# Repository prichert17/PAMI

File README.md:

# Projet PAMI (2025-2026) - Eurobot

Ce dépôt documente le projet PAMI (Petit Actionneur Motorisé Indépendant) sur lequel j'ai travaillé pendant un an, dans le cadre de la coupe Eurobot 2026. Il centralise l'ensemble de la conception matérielle (deux PCB, structure mécanique) et logicielle du robot. 

<p align="center">
  
  <br>
  <em>Légende : Photo du robot PAMI assemblé</em>
</p>

<p align="center">
  
  <br>
  <em>Légende : Rendu 3D du robot (Fusion 360)</em>
</p>

## Codes principaux

Pour mieux comprendre l'architecture du système, voici les trois éléments importants du dépôt :

*   **[`PAMI_2026/`](./Projects/PAMI_2026)** : Contient le code haut niveau qui est exécuté sur le microcontrôleur **ESP32**.
*   **[`Projects/Asservissement_G4/`](./Projects/Asservissement_G4)** : Contient tout le code de l'asservissement, de l'odométrie et le contrôle des moteurs. Ce code tourne sur la carte **NUCLEO-G431KB** (STM32).
*   **[`Projects/IHM_PAMI_2026.py`](./Projects/IHM_PAMI_2026.py)** : Une interface homme-machine (IHM) développée en Python qui permet de lire et visualiser en temps réel les coordonnées et l'état du PAMI lors des phases de tests.

---

## Architecture Bas Niveau : PCB Principal (Contrôle Moteurs & Alimentation)

Le robot dispose de deux cartes électroniques (PCB). La partie bas niveau, gérée par le PCB principal s'occupe de l'alimentation générale et de la motricité du robot. Le PAMI est assez compact : ses dimensions finales sont de 10.5cm par 19cm avec ses bras repliés (et 24cm bras dépliés), ce qui a imposé des contraintes sur le routage du circuit et le choix des composants.

### 1. Gestion de la Batterie et Alimentation
Le robot est alimenté par une unique cellule de batterie LiFePO4 au format 26650. Le circuit d'alimentation a subi plusieurs modifications suite à des problèmes rencontrés lors du développement :

*   **Le choix du LiFePO4 :** Bien que l'intégration de cette chimie ait rendu la conception du circuit d'alimentation plus complexe (notamment pour la régulation de tension, le prix plus élevé), c'est un choix qui reste très avantageux. Le LiFePO4 est extrêmement sécurisé (aucun risque d'incendie, pas besoin de sac ignifugé contrairement aux batteries LiPo), il offre un excellent courant de décharge (15A) pour les moteurs, et l'utilisation d'une seule et unique cellule simplifie grandement le processus de charge (pas d'équilibrage entre deux cellules nécessaire).
*   **Port USB C intégré :** Pour une simplicité d'usage maximale, un port USB C standard a été intégré au design, permettant de recharger facilement la batterie avec n'importe quel chargeur ou batterie externe.
*   **Circuit de Charge :** La charge est gérée directement sur le PCB par un composant dédié à ce type de batterie, le **CN3058E**, avec des LEDs indicatrices (Charge en cours / Charge terminée).
*   **Sécurité Batterie :** La batterie est surveillée par un IC de protection **HY2112**, associé à un double MOSFET N-Channel (FS8205A) pour couper le circuit en cas de problème.
*   **Régulation de tension :** La tension de la cellule LiFePO4 pouvant monter à 3.6V (ce qui est trop élevé pour l'ESP32 et certains capteurs), j'ai opté pour un convertisseur **Buck-Boost (TPS63000)** au lieu d'un simple circuit Boost. Il assure un 3.3V parfaitement stable en abaissant ou élevant la tension de la batterie selon les besoins, pour un courant jusqu'à 1A.
*   **Le problème des appels de courant :** Un problème est survenu avec l'alimentation des servomoteurs. Leurs appels de courant créaient d'énormes chutes de tension (la tension de la batterie chutait jusqu'à 2.4V pendant un court instant). Le robot ne parvenait pas à se lever de manière autonome, la tension de la batterie passait en dessous du seuil limite du circuit boost 6V. La cause : la résistance interne du boitier de la batterie 26650 et des pistes de cuivre trop fines (1.5mm) qui ne supportaient pas les pics d'intensité très élevés (pouvant monter jusqu'à 3A sur le rail 6V, soit quasiment 6A en sortie de la batterie). Le problème a été résolu en soudant un condensateur de 2200µF (10V) directement à l'entrée du boost 6V pour agir comme une réserve d'énergie, ce qui diminuait fortement la chute de tension.

### 2. Odométrie et Asservissement (NUCLEO-G431KB)
La carte intègre un microcontrôleur STM32 (NUCLEO-G431KB) programmé en C++ pour gérer la dynamique temps-réel du robot. Un travail conséquent a été réalisé sur la fiabilité des déplacements et la prévention du patinage.

*   **Odométrie Haute Fréquence (500Hz) :** La position exacte du robot (X, Y, Angle) est calculée 500 fois par seconde. Les encodeurs incrémentiels des roues renvoient des signaux en quadrature décodés de manière purement matérielle par les Timers du STM32. Le code gère les débordements de compteurs (overflow des timers 16 bits) pour assurer un suivi sans erreur.
*   **Asservissement PID en 2 Phases (100Hz) :** Le contrôle de la trajectoire s'effectue via une boucle PID (Proportionnel, Intégral, Dérivé) actualisée à 100Hz. Pour rejoindre une cible, l'algorithme utilise une logique en deux temps :
    1. **Rotation pure :** Le robot pivote sur lui-même pour s'aligner parfaitement vers sa cible.
    2. **Avance avec correction :** Une fois aligné, il avance en ligne droite tout en maintenant son angle de manière active. Si le robot doit dévier fortement, la commande linéaire est automatiquement réduite pour privilégier la rotation et garder un mouvement fluide.
*   **Traction Control & Anti-Patinage :** Les robots de la coupe Eurobot sont sujets au patinage (poussière, accélération forte), ce qui fausse instantanément l'odométrie. J'ai donc un algorithme de détection de glissement : si la différence de vitesse mesurée entre la roue gauche et droite devient anormalement élevée, le STM32 détecte la perte d'adhérence et réduit la commande PWM envoyée aux moteurs.
*   **Performances :** À pleine vitesse, les moteurs tournent à environ 5 tours/seconde, propulsant le PAMI à 68 cm/s (2.4 km/h). La dérive odométrique pure a été mesurée à environ 2cm d'erreur pour 1 mètre parcouru en ligne droite.
*   **Communication Inter-Cartes :** Le STM32 transmet continuellement ses données d'odométrie et son état au cerveau central (l'ESP32) via une liaison série (UART), dont le protocole est détaillé dans `pami_com.h`.

<p align="center">
  
  <br>
  <em>Légende : Schéma de l'architecture d'asservissement du STM32.</em>
</p>

### Schématique du PCB Principal

Voici la schématique électrique du PCB principal (Moteurs & Alimentation) montrant l'interconnexion entre la NUCLEO, les drivers moteurs, le circuit de charge de la batterie et le régulateur Buck-Boost :

<p align="center">
  
  <br>
  <em>Légende : Schématique détaillée du PCB d'alimentation</em>
</p>

<p align="center">
  
  <br>
  <em>Légende : Routage du PCB d'alimentation</em>
</p>

## Architecture Haut Niveau : Capteurs et Stratégie (ESP32)

La seconde carte du robot embarque un **ESP32**. Ce microcontrôleur fait office de cerveau principal : il ne gère pas les moteurs principaux directement, mais s'occupe de la prise de décision, de la vision spatiale (capteurs ToF matriciels), de la gestion du temps de match et de l'interface utilisateur.

### 1. Multitâche avec FreeRTOS
Pour garantir une réactivité maximale sans bloquer le système lors de la lecture des capteurs I2C (qui peut être lente), le code de l'ESP32 est architecturé autour du système d'exploitation temps réel **FreeRTOS**. Les tâches sont réparties sur les deux cœurs (Cores) physiques du processeur :

*   **Core 1 (Haute Priorité) :** 
    *   `Task_Comms` : Écoute en continu le port série UART pour ne rater aucune mise à jour de position venant du STM32. Permet aussi le debug lorsque branché à un PC.
    *   `Task_Strategy` : La machine à états principale du robot. Elle dicte les déplacements et gère le chronomètre du match.
*   **Core 0 (Basse Priorité) :**
    *   `Task_Tofs` : Gère le multiplexage et l'acquisition des données des 3 capteurs de distance matriciels sur le bus I2C.
    *   `Task_IHM` : Contrôle les animations de la LED d'état WS2812B et pilote les servomoteurs d'actionnement de fin de match.

### 2. Vision Spatiale : Capteurs ToF (VL53L5CX) et Anti-Collision
Le robot est équipé de 3 capteurs Time-of-Flight matriciels **VL53L5CX** (Centre, Gauche, Droite) configurés en résolution 8x8 zones à 15 Hz.

*  L'ESP32 configure dynamiquement les adresses I2C des 3 capteurs au démarrage (vers `0x30`, `0x31`, `0x32`) en utilisant les broches `XSHUT` (LPN), ce qui permet de tous les utiliser sur le même bus I2C à 400kHz.
*   **Calcul de repère absolu :** Lorsqu'un capteur détecte un obstacle, la tâche ne se contente pas de renvoyer une distance. Elle utilise la position instantanée du robot (X, Y, θ) et la géométrie des capteurs (FOV de 45°/60°, offset physique en X/Y) pour projeter l'obstacle sur le système de coordonnées du terrain. Le robot sait exactement où se trouve l'obstacle sur la table.
*   **Évitement d'urgence :** Si un objet est détecté à moins de 10 cm dans les zones critiques, le STM32 reçoit instantanément un ordre d'arrêt (`stopMotors()`) via l'UART. Le robot se met en pause et reprend sa route de lui-même dès que l'obstacle disparaît.

### 3. Stratégie et Machine à États
La logique de match est dictée par une machine à états :

1.  **`STATE_WAIT` (Attente) :** L'ESP32 lit la couleur de l'équipe via un switch (`PIN_SW_COLOR`). L'ensemble du système de coordonnées (points de départ, waypoints, cibles) est automatiquement symétrisée (inversion de l'axe X) si le robot est dans l'équipe bleue. Le robot attend le retrait de la tirette, en affichant la couleur du terrain sur la led d'IHM.
2.  **`STATE_DELAY` (Attente 85s) :** Selon les règles, les PAMI ne peuvent entrer en action qu'à la fin du match principal. Au retrait de la tirette, le robot reset son odométrie (`resetSTM32`) puis attend pendant 85 secondes.
3.  **`STATE_GAME` (Match) :** L'ESP32 commence à lire sa route de Waypoints et envoie les coordonnées cibles au STM32. Si un obstacle fixe est détecté lors du premier déplacement, un waypoint bonus est généré dynamiquement pour modifier la stratégie en cours de match.
4.  **`STATE_END` (Fin de match) :** À T+99s, le robot stoppe ses moteurs et déploie ses bras à l'aide de ses servomoteurs.

### 4. Communication Inter-Cartes et IHM
*   **Protocole UART :** L'ESP32 et le STM32 communiquent à 115200 bauds. Le STM32 "stream" en continu ses coordonnées au format `X:123,Y:456,Z:1.57`, que l'ESP32 parse via la fonction `parseSTM32Data`. En retour, l'ESP32 envoie des commandes simples au STM32 (`mode auto`, `stop`, `X:1000`, `reset:x:y:z`).
*   **Feedback Visuel (LED WS2812B) :** Sans écran, le debug visuel repose principalement sur la LED RGB adressable intelligente. Sa couleur et son rythme de clignotement indiquent instantanément l'état du système : 
    *   *Rouge fixe* : Batterie LiFePO4 faible.
    *   *Orange clignotant* : Obstacle détecté par ToF.
    *   *Vert clignotant* : Tirette retirée, en cours d'attente (85s).
    *   *Vert fixe* : Match en cours.
    *   *Jaune/Bleu* : Robot en attente de la tirette, affiche la couleur de l'équipe sélectionnée.

### 5. Conception de la Carte ESP32 (PCB Haut Niveau)
Pour centraliser toutes ces fonctionnalités, un second PCB a été conçu spécifiquement pour accueillir l'ESP32. Cette carte vient se superposer à la carte d'alimentation principale et gère toute la logique périphérique :

*   **L'Interface Utilisateur (Switchs et LED) :** La carte intègre directement 3 interrupteurs (`DEBUG` pour l'affichage des logs, `TERRAIN` pour le choix de la couleur, et `MODE` pour basculer entre le mode automatique et le contrôle manuel via manette bluetooth), le connecteur pour la `Tirette` de démarrage, ainsi que la LED d'état WS2812B.
*   **Les Capteurs ToF :** Le routage contient aussi les 3 capteurs VL53L5CX (avec les angles adéquats pour couvrir l'avant du robot). On y retrouve le bus I2C commun (SDA/SCL) ainsi que les broches dédiées `LPN1`, `LPN2`, et `LPN3` permettant d'allumer les capteurs séquentiellement pour modifier leur adresse I2C au boot.
*   **Les Actionneurs (Servomoteurs) :** 3 connecteurs pour servomoteurs (`SERVO m1`, `SERVO m2`, `SERVO m3`) sont présents. Ils sont alimentés directement par le rail **6V** provenant de la carte principale, et commandés par des broches PWM de l'ESP32. Des condensateurs de 100µF sont placés au plus près des connecteurs pour lisser les appels de courant.
*   **Interconnexion :** Le connecteur `COMM_inter_mcu` assure la liaison avec la carte STM32 pour l'UART (TX/RX), les alimentations (3.3V et 6V), et les deux moteurs auxiliaires posés sur l'actionneur du robot qui lui permette de gravire des obstacles.

Voici la schématique et le routage de cette seconde carte :

<p align="center">
  
  <br>
  <em>Légende : Schématique détaillée du PCB ESP32 (Capteurs, IHM, Servos)</em>
</p>

<p align="center">
  
  <br>
  <em>Légende : Routage du PCB ESP32</em>
</p>

---

## Conclusion et Démonstration en Match

Après de nombreuses itérations matérielles (sur les deux itérations de PCB et la mécanique) ainsi qu'un gros travail d'optimisation logicielle, le PAMI a su remplir son rôle de manière fiable et concluante.

Voici une courte vidéo démontrant son fonctionnement lors d'un match (cas le plus simple, sans obstacles) :

https://github.com/user-attachments/assets/42d38b15-34ad-48e5-a77b-8a1eeed6a4e9

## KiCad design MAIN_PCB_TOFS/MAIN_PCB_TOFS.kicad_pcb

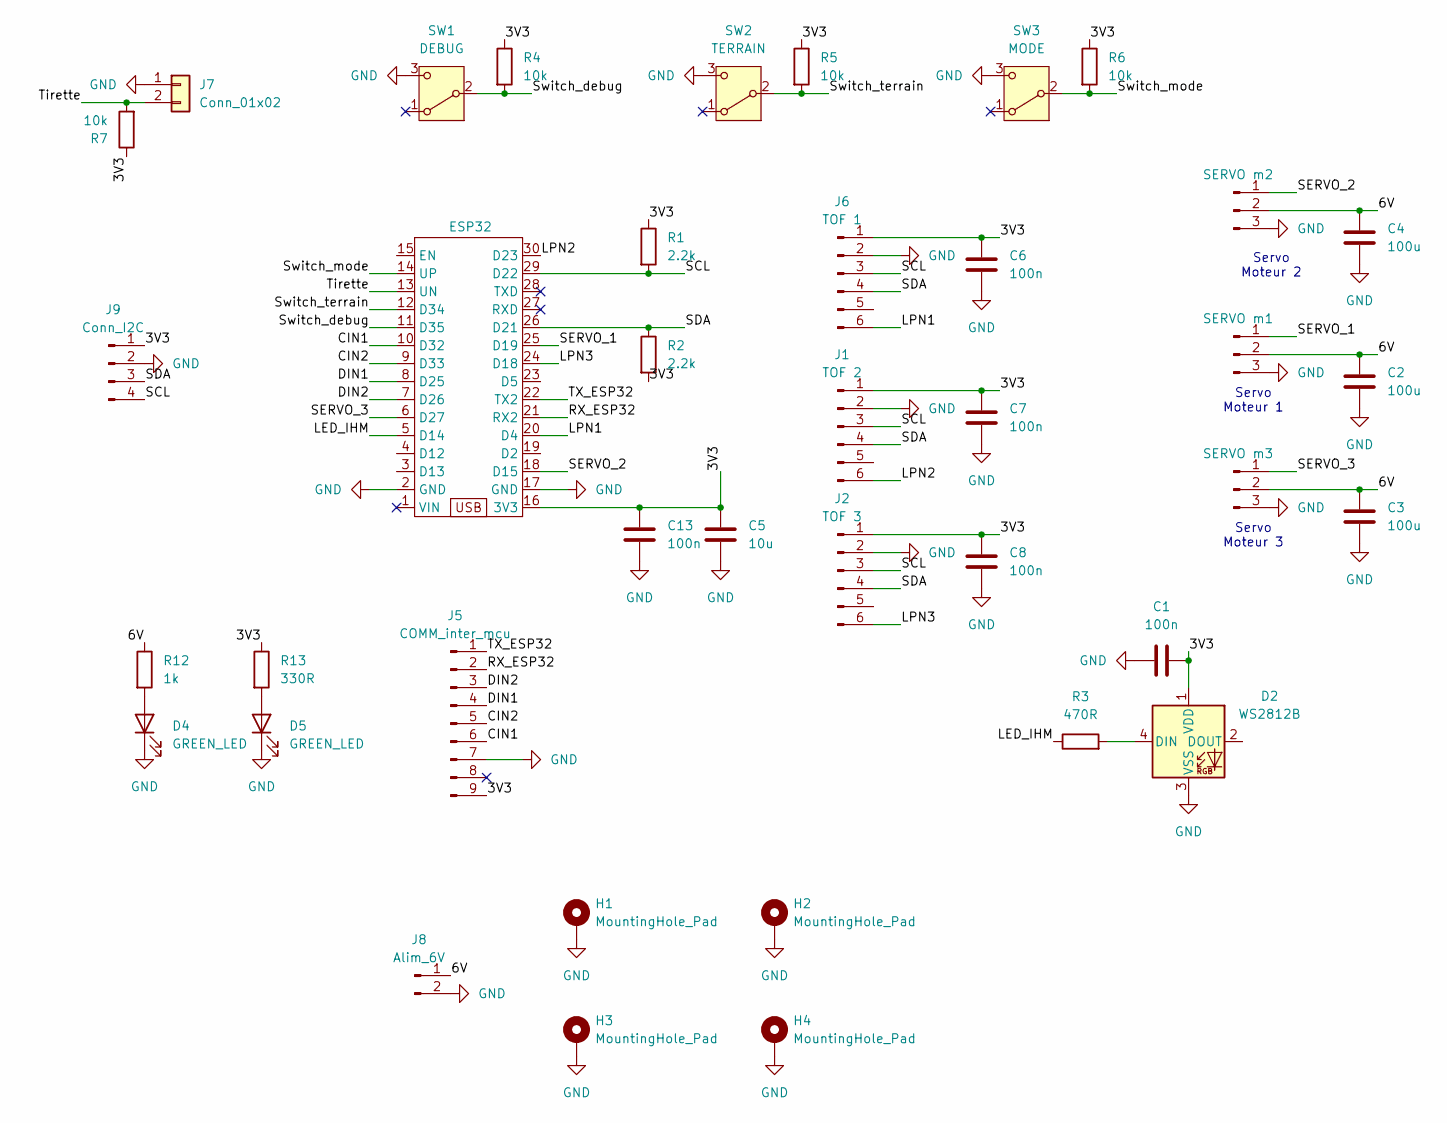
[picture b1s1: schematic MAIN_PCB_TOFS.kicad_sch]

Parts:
C1, C6, C7, C8, C13: 100n; C_0603_1608Metric
C2, C3, C4: 100u; CP_Elec_6.3x5.8
C5: 10u; C_0603_1608Metric
D2: WS2812B; LED_WS2812B_PLCC4_5.0x5.0mm_P3.2mm
D4, D5: GREEN_LED; LED_0603_1608Metric
H1, H2, H3, H4: MountingHole_Pad; MountingHole_3.2mm_M3_Pad_Via
J1: TOF 2; PinHeader_1x06_P2.54mm_Vertical
J2: TOF 3; PinHeader_1x06_P2.54mm_Vertical
J3: SERVO m2; PinHeader_1x03_P2.54mm_Vertical
J4: SERVO m1; PinHeader_1x03_P2.54mm_Vertical
J5: COMM_inter_mcu; PinSocket_1x09_P2.54mm_Vertical
J6: TOF 1; PinHeader_1x06_P2.54mm_Vertical
J7: Conn_01x02; PinHeader_1x02_P2.54mm_Vertical
J8: Alim_6V; JST_VH_B2P-VH_1x02_P3.96mm_Vertical
J9: Conn_I2C; PinHeader_1x04_P2.54mm_Vertical
J12: SERVO m3; PinHeader_1x03_P2.54mm_Vertical
R1, R2: 2.2k; R_0603_1608Metric
R3: 470R; R_0603_1608Metric
R4, R5, R6, R7: 10k; R_0603_1608Metric
R12: 1k; R_0603_1608Metric
R13: 330R; R_0603_1608Metric
SW1: DEBUG; SW_SPDT_PCM12
SW2: TERRAIN; SW_SPDT_PCM12
SW3: MODE; SW_SPDT_PCM12
U1: ESP32; DIP-30_W25.4mm_LongPads_esp32

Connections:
/3V3: C1.2, C5.1, C6.1, C7.1, C8.1, C13.1, D2.1 (VDD), J1.1, J2.1, J5.9, J6.1, J9.1, R1.1, R2.2, R4.1, R5.1, R6.1, R7.1, R13.1, U1.16 (3V3)
/6V: C2.1, C3.1, C4.1, J3.2, J4.2, J8.1, J12.2, R12.1
/CIN1: J5.6, U1.10 (D32)
/CIN2: J5.5, U1.9 (D33)
/DIN1: J5.4, U1.8 (D25)
/DIN2: J5.3, U1.7 (D26)
/LED_IHM: R3.1, U1.5 (D14)
/LPN1: J6.6, U1.20 (D4)
/LPN2: J1.6, U1.30 (D23)
/LPN3: J2.6, U1.24 (D18)
/RX_ESP32: J5.2, U1.21 (RX2)
/SCL: J1.3, J2.3, J6.3, J9.4, R1.2, U1.29 (D22)
/SDA: J1.4, J2.4, J6.4, J9.3, R2.1, U1.26 (D21)
/SERVO_1: J4.1, U1.25 (D19)
/SERVO_2: J3.1, U1.18 (D15)
/SERVO_3: J12.1, U1.6 (D27)
/Switch_debug: R4.2, SW1.2 (B), U1.11 (D35)
/Switch_mode: R6.2, SW3.2 (B), U1.14 (UP)
/Switch_terrain: R5.2, SW2.2 (B), U1.12 (D34)
/TX_ESP32: J5.1, U1.22 (TX2)
/Tirette: J7.2, R7.2, U1.13 (UN)
GND: C1.1, C2.2, C3.2, C4.2, C5.2, C6.2, C7.2, C8.2, C13.2, D2.3 (VSS), D4.1 (K), D5.1 (K), H1.1, H2.1, H3.1, H4.1, J1.2, J2.2, J3.3, J4.3, J5.7, J6.2, J7.1, J8.2, J9.2, J12.3, SW1.3 (C), SW2.3 (C), SW3.3 (C), U1.2 (GND), U1.17 (GND)
unnamed: D2.4 (DIN), R3.2
unnamed: D4.2 (A), R12.2
unnamed: D5.2 (A), R13.2

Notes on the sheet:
Servo Moteur 2
Servo Moteur 1
Servo Moteur 3

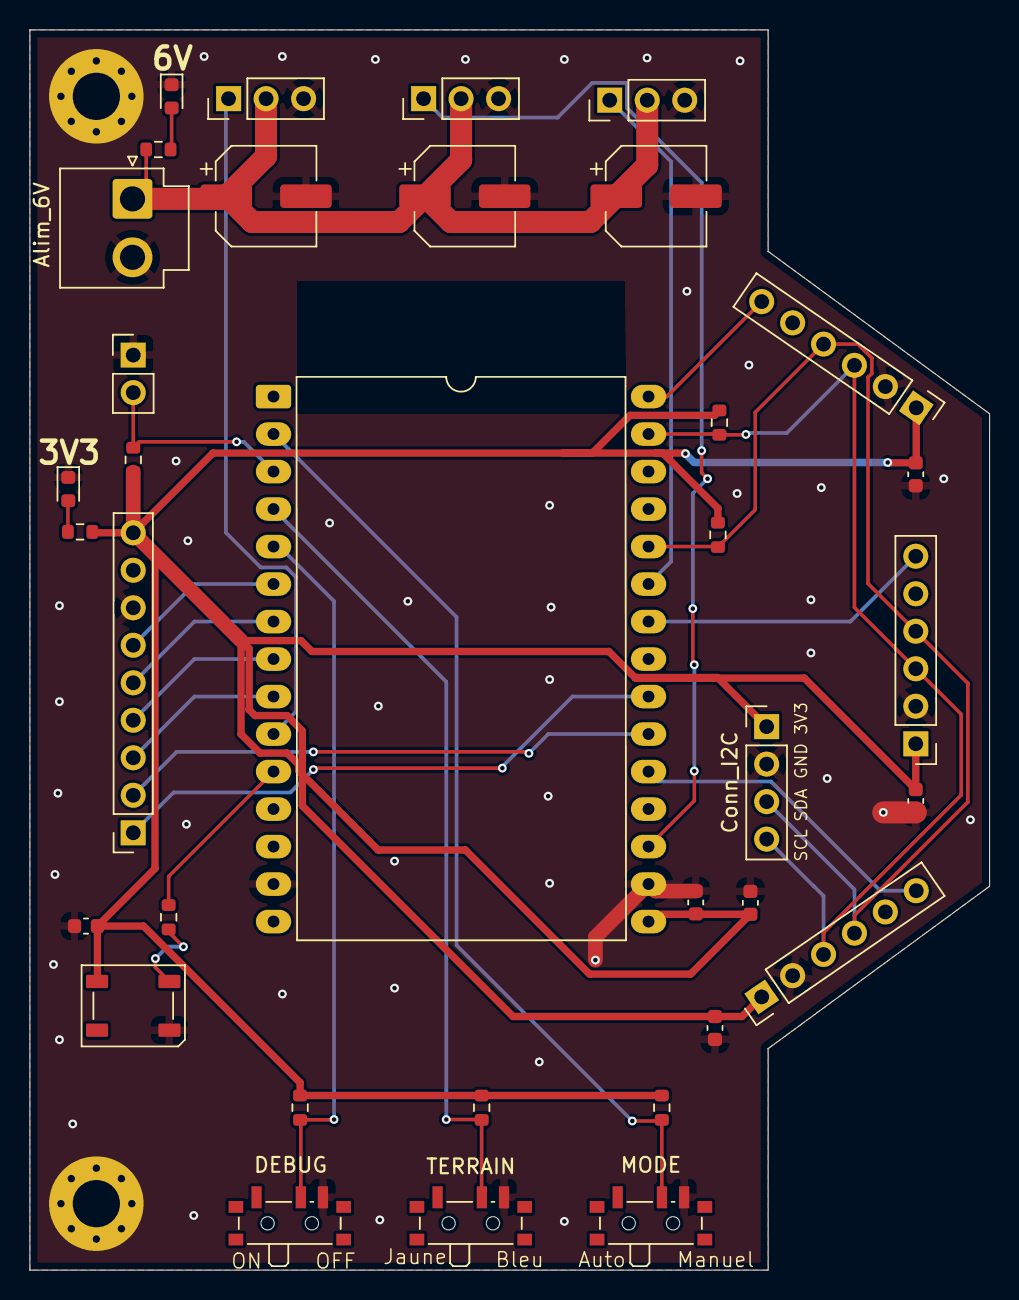
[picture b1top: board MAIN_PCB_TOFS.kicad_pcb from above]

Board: 2 copper layers, 65.0 x 84.0 mm, 37 parts (0 on the bottom side), 25 nets.

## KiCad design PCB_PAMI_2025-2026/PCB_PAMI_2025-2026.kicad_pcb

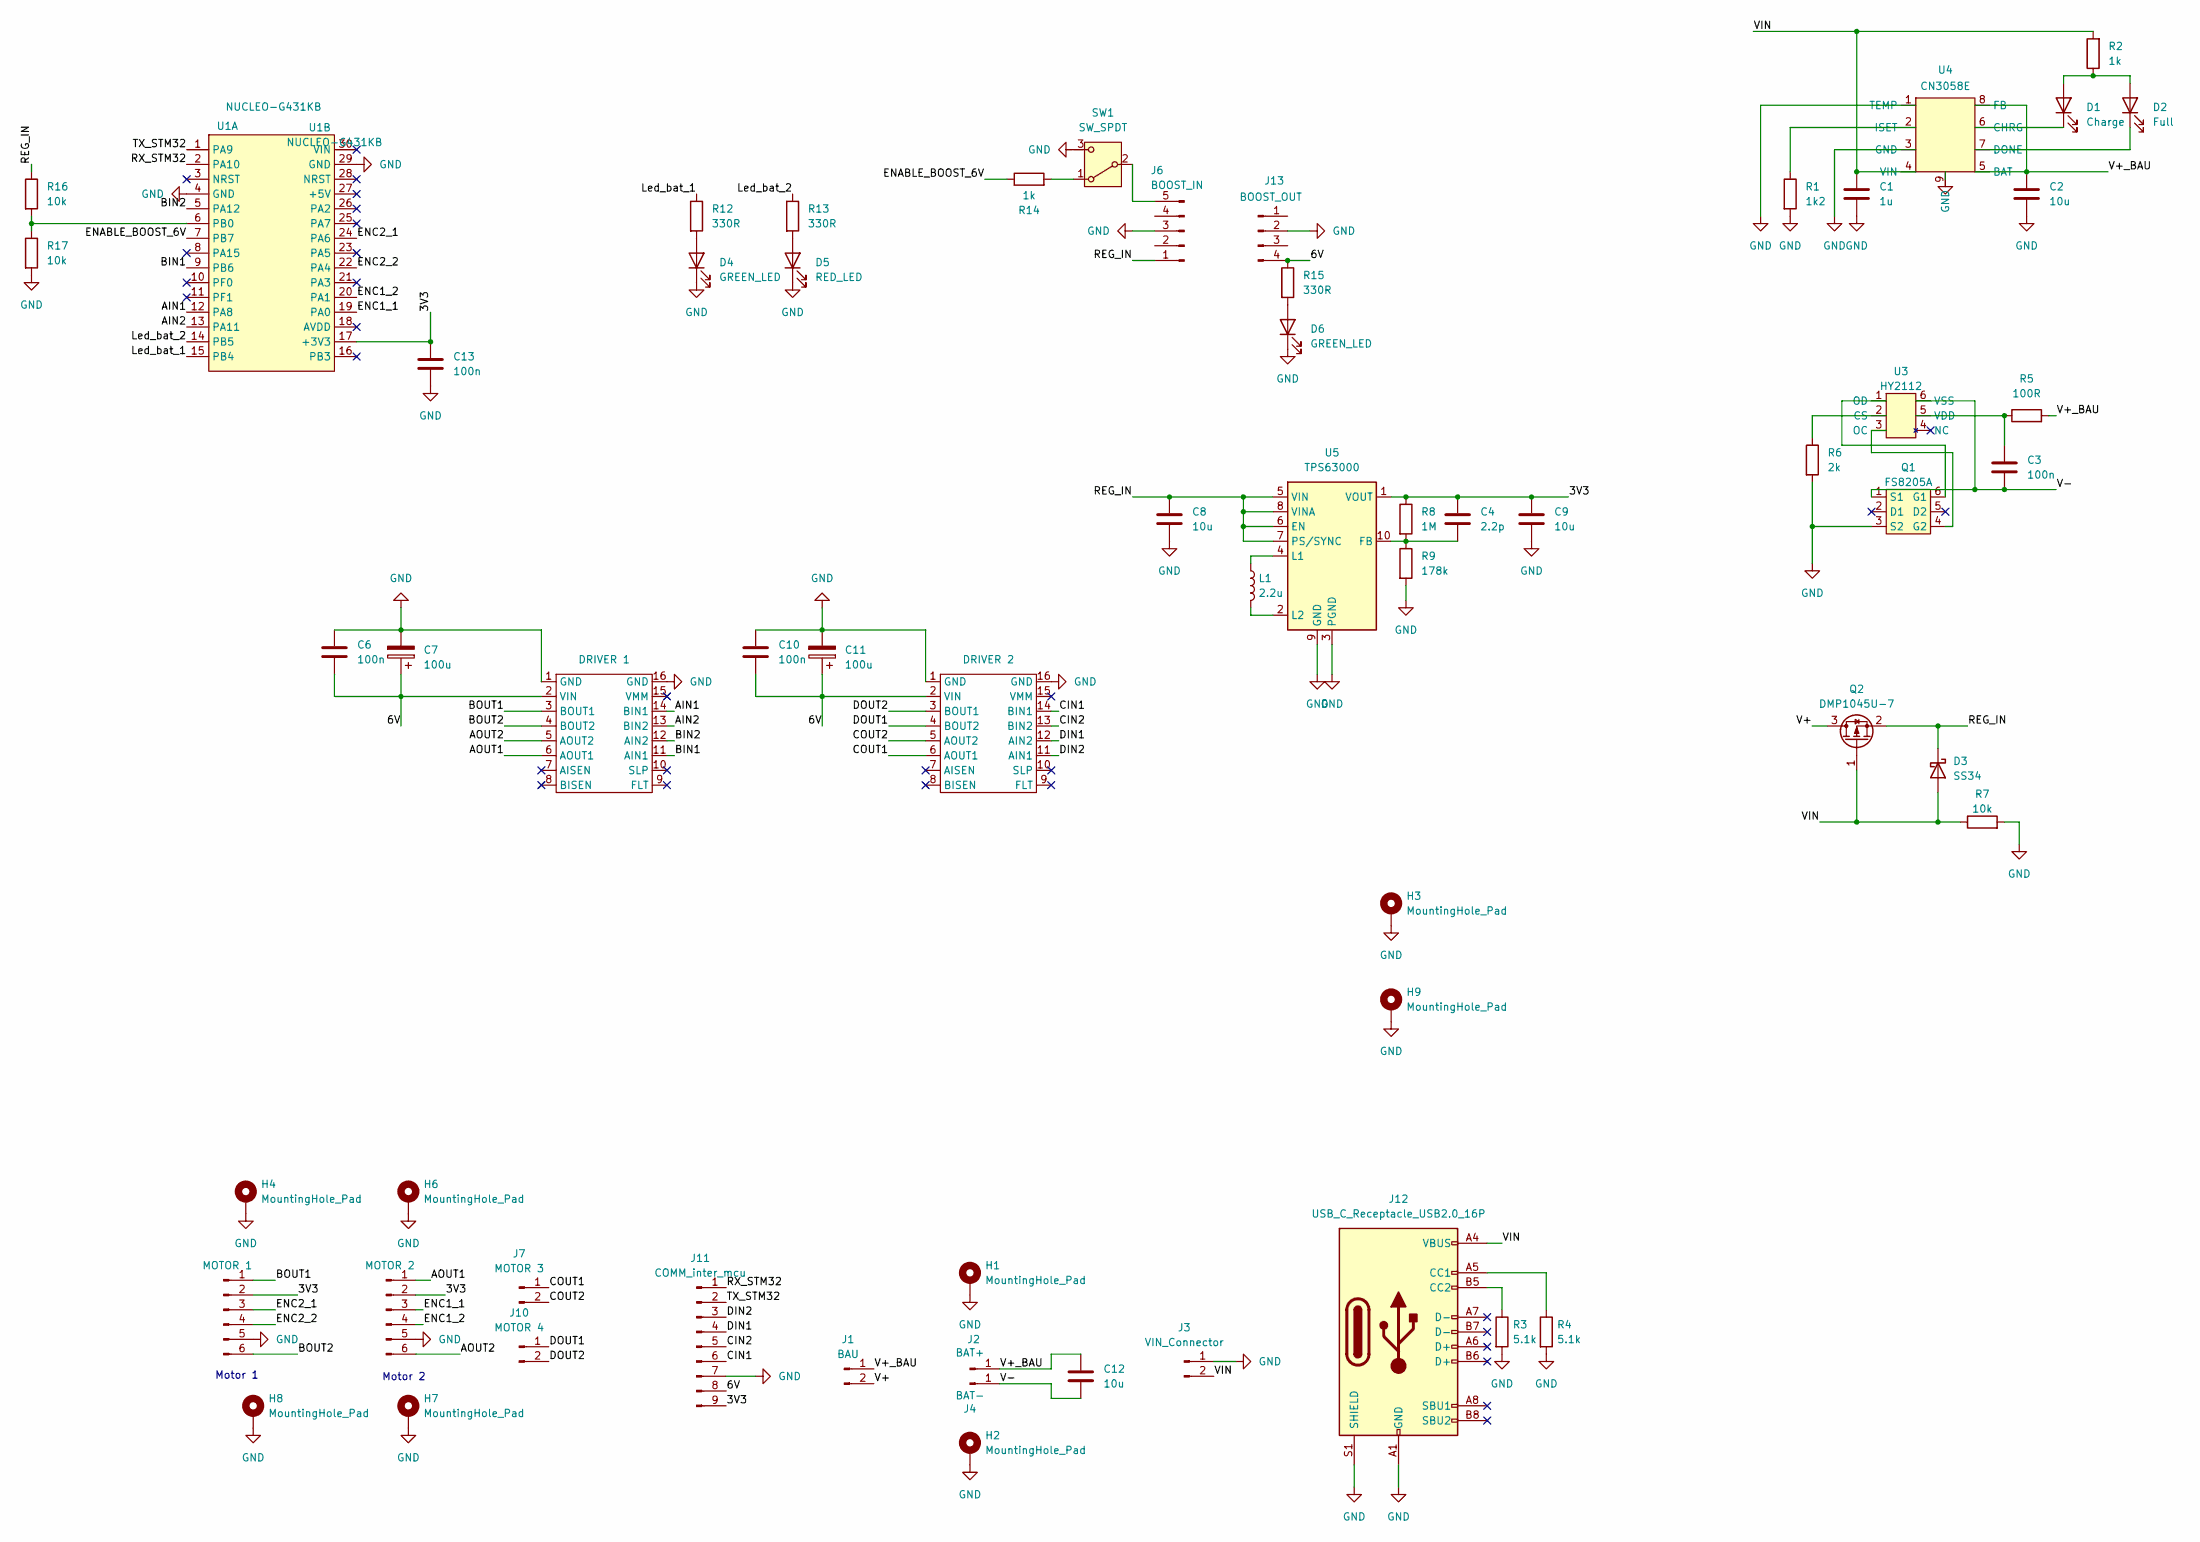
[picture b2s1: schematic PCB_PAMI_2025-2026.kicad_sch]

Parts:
C1: 1u; C_0603_1608Metric
C2, C8, C9, C12: 10u; C_0603_1608Metric
C3, C6, C10, C13: 100n; C_0603_1608Metric
C4: 2.2p; C_0603_1608Metric
C7, C11: 100u; CP_Elec_6.3x5.4
D1: Charge; LED_0603_1608Metric
D2: Full; LED_0603_1608Metric
D3: SS34; D_SMA
D4, D6: GREEN_LED; LED_0603_1608Metric
D5: RED_LED; LED_0603_1608Metric
H1, H2, H3, H4, H6, H7, H8, H9: MountingHole_Pad; MountingHole_3.2mm_M3_Pad_Via
J1: BAU; JST_VH_B2P-VH_1x02_P3.96mm_Vertical
J2: BAT+; TestPoint_THTPad_D2.5mm_Drill1.2mm
J3: VIN_Connector; TerminalBlock_Phoenix_MKDS-1,5-2-5.08_1x02_P5.08mm_Horizont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
J4: BAT-; TestPoint_THTPad_D2.5mm_Drill1.2mm
J6: BOOST_IN; PinSocket_1x05_P2.54mm_Vertical
J7: MOTOR 3; JST_VH_B2P-VH_1x02_P3.96mm_Vertical
J8: MOTOR 1; PinHeader_1x06_P2.54mm_Vertical
J9: MOTOR 2; PinHeader_1x06_P2.54mm_Vertical
J10: MOTOR 4; JST_VH_B2P-VH_1x02_P3.96mm_Vertical
J11: COMM_inter_mcu; PinSocket_1x09_P2.54mm_Vertical
J12: USB_C_Receptacle_USB2.0_16P; USB_C_Receptacle_HRO_TYPE-C-31-M-12
J13: BOOST_OUT; PinSocket_1x04_P2.54mm_Vertical
L1: 2.2u; L_Wuerth_WE-TPC-3816
Q1: FS8205A; SOT-23-6
Q2: DMP1045U-7; SOT-23
R1: 1k2; R_0603_1608Metric
R2, R14: 1k; R_0603_1608Metric
R3, R4: 5.1k; R_0603_1608Metric
R5: 100R; R_0603_1608Metric
R6: 2k; R_0603_1608Metric
R7, R16, R17: 10k; R_0603_1608Metric
R8: 1M; R_0603_1608Metric
R9: 178k; R_0603_1608Metric
R12, R13, R15: 330R; R_0603_1608Metric
SW1: SW_SPDT; SW_SPDT_PCM12
U1: NUCLEO-G431KB; Arduino_Nano
U2: DRIVER 1; DIP-16_W10.16mm_LongPads
U3: HY2112; SOT-23-6
U4: CN3058E; SOIC-8-1EP_3.9x4.9mm_P1.27mm_EP2.29x3mm
U5: TPS63000; Texas_DRC0010J_ThermalVias
U6: DRIVER 2; DIP-16_W10.16mm_LongPads

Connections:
/3V3: C4.1, C9.1, C13.1, J8.2, J9.2, J11.9, R8.1, U1.17 (+3V3), U5.1 (VOUT)
/6V: C6.2, C7.1, C10.2, C11.1, J11.8, J13.4, R15.1, U2.2 (VIN), U6.2 (VIN)
/AIN1: U1.12 (PA8), U2.14 (BIN1)
/AIN2: U1.13 (PA11), U2.13 (BIN2)
/AOUT1: J9.1, U2.6 (AOUT1)
/AOUT2: J9.6, U2.5 (AOUT2)
/BIN1: U1.9 (PB6), U2.11 (AIN1)
/BIN2: U1.5 (PA12), U2.12 (AIN2)
/BOUT1: J8.1, U2.3 (BOUT1)
/BOUT2: J8.6, U2.4 (BOUT2)
/CIN1: J11.6, U6.14 (BIN1)
/CIN2: J11.5, U6.13 (BIN2)
/COUT1: J7.1, U6.6 (AOUT1)
/COUT2: J7.2, U6.5 (AOUT2)
/DIN1: J11.4, U6.12 (AIN2)
/DIN2: J11.3, U6.11 (AIN1)
/DOUT1: J10.1, U6.4 (BOUT2)
/DOUT2: J10.2, U6.3 (BOUT1)
/ENABLE_BOOST_6V: R14.1, U1.7 (PB7)
/ENC1_1: J9.3, U1.19 (PA0)
/ENC1_2: J9.4, U1.20 (PA1)
/ENC2_1: J8.3, U1.24 (PA6)
/ENC2_2: J8.4, U1.22 (PA4)
/Led_bat_1: R12.1, U1.15 (PB4)
/Led_bat_2: R13.1, U1.14 (PB5)
/REG_IN: C8.1, D3.1 (K), J6.1, Q2.2 (S), R16.1, U5.5 (VIN), U5.6 (EN), U5.7 (PS/SYNC), U5.8 (VINA)
/RX_STM32: J11.1, U1.2 (PA10)
/TX_STM32: J11.2, U1.1 (PA9)
/V+: J1.2, Q2.3 (D)
/V+_BAU: C2.1, C12.1, J1.1, J2.1, R5.2, U4.5 (BAT), U4.8 (FB)
/V-: C3.2, C12.2, J4.1, Q1.1 (S1), U3.6 (VSS)
/VIN: C1.1, D3.2 (A), J3.2, J12.A4 (VBUS), J12.A9 (VBUS), J12.B4 (VBUS), J12.B9 (VBUS), Q2.1 (G), R2.2, R7.1, U4.4 (VIN)
GND: C1.2, C2.2, C6.1, C7.2, C8.2, C9.2, C10.1, C11.2, C13.2, D4.1 (K), D5.1 (K), D6.1 (K), H1.1, H2.1, H3.1, H4.1, H6.1, H7.1, H8.1, H9.1, J3.1, J6.3, J8.5, J9.5, J11.7, J12.A1 (GND), J12.A12 (GND), J12.B1 (GND), J12.B12 (GND), J12.S1 (SHIELD), J13.2, Q1.3 (S2), R1.2, R3.2, R4.2, R6.2, R7.2, R9.2, R17.2, SW1.3 (C), U1.4 (GND), U1.29 (GND), U2.1 (GND), U2.16 (GND), U4.1 (TEMP), U4.3 (GND), U4.9 (GND), U5.3 (PGND), U5.9 (GND), U5.11 (PGND), U6.1 (GND), U6.16 (GND)
unnamed: D1.2 (A), D2.2 (A), R2.1
unnamed: D1.1 (K), U4.6 (CHRG)
unnamed: D2.1 (K), U4.7 (DONE)
unnamed: D4.2 (A), R12.2
unnamed: D5.2 (A), R13.2
unnamed: D6.2 (A), R15.2
unnamed: J6.5, SW1.2 (B)
unnamed: J12.A5 (CC1), R4.1
unnamed: J12.B5 (CC2), R3.1
unnamed: Q1.6 (G1), U3.1 (OD)
unnamed: Q1.4 (G2), U3.3 (OC)
unnamed: R14.2, SW1.1 (A)
unnamed: R16.2, R17.1, U1.6 (PB0)
unnamed: R6.1, U3.2 (CS)
unnamed: C3.1, R5.1, U3.5 (VDD)
unnamed: R1.1, U4.2 (ISET)
unnamed: C4.2, R8.2, R9.1, U5.10 (FB)
unnamed: L1.1, U5.4 (L1)
unnamed: L1.2, U5.2 (L2)

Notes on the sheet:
Motor 1
Motor 2

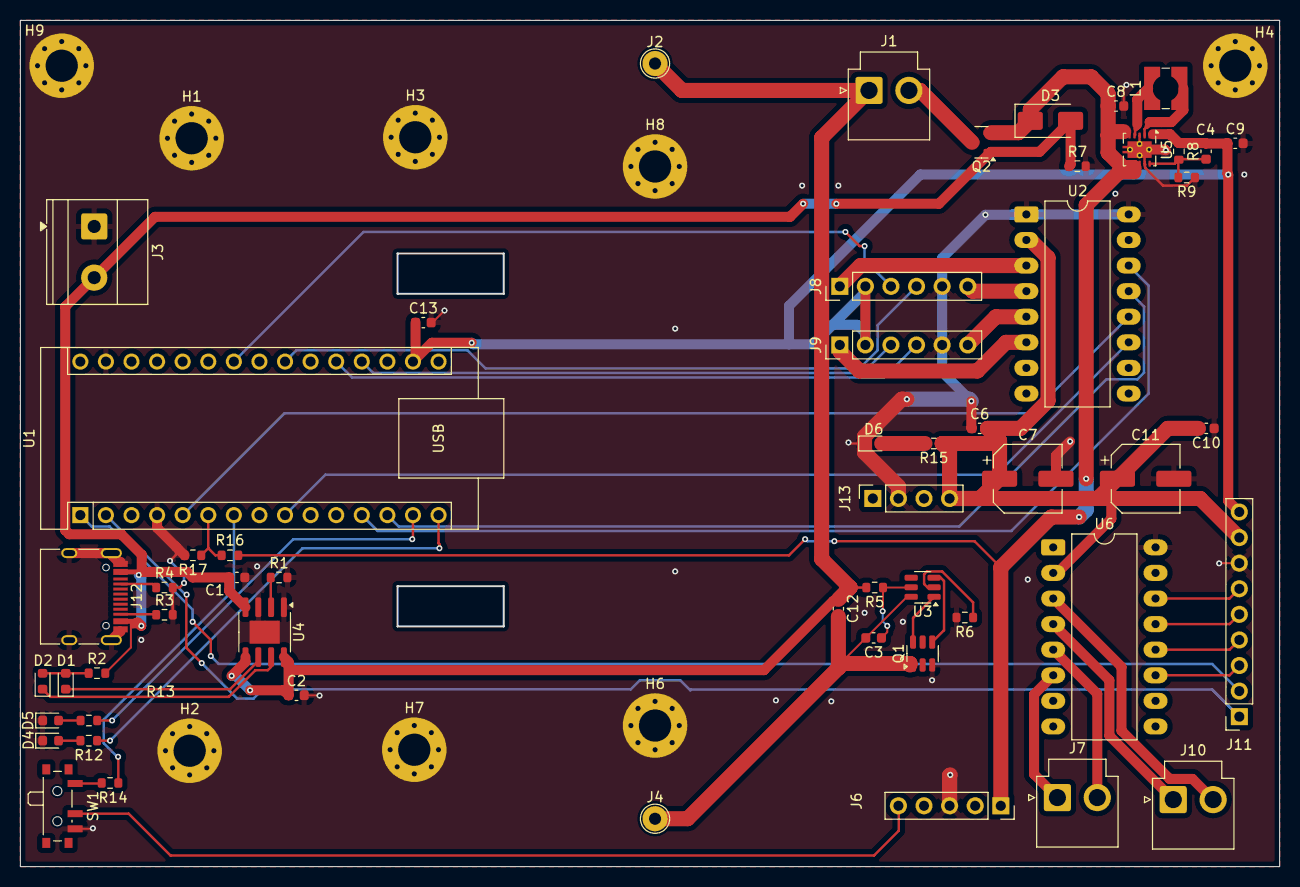
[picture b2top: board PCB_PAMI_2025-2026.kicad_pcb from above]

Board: 2 copper layers, 124.9 x 83.9 mm, 63 parts (0 on the bottom side), 52 nets.

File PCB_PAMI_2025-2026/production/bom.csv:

Designator,Footprint,Quantity,Value,LCSC Part #
C1,0603,1,1u,
"C10, C13, C3, C6",0603,4,100n,
"C11, C7",CP_Elec_6.3x5.4,2,100u,
"C12, C2, C8, C9",0603,4,10u,
C4,0603,1,2.2p,
D1,0603,1,Charge,
D2,0603,1,Full,
D3,D_SMA,1,SS34,
"D4, D6",0603,2,GREEN_LED,
D5,0603,1,RED_LED,
J1,JST_VH_B2P-VH_1x02_P3.96mm_Vertical,1,BAU,
J10,JST_VH_B2P-VH_1x02_P3.96mm_Vertical,1,MOTOR 4,
J11,PinSocket_1x09_P2.54mm_Vertical,1,COMM_inter_mcu,
J12,USB_C_Receptacle_HRO_TYPE-C-31-M-12,1,USB_C_Receptacle_USB2.0_16P,
J13,PinSocket_1x04_P2.54mm_Vertical,1,BOOST_OUT,
J2,TestPoint_THTPad_D2.5mm_Drill1.2mm,1,BAT+,
J3,"TerminalBlock_Phoenix_MKDS-1,5-2-5.08_1x02_P5.08mm_Horizontal",1,VIN_Connector,
J4,TestPoint_THTPad_D2.5mm_Drill1.2mm,1,BAT-,
J6,PinSocket_1x05_P2.54mm_Vertical,1,BOOST_IN,
J7,JST_VH_B2P-VH_1x02_P3.96mm_Vertical,1,MOTOR 3,
J8,PinHeader_1x06_P2.54mm_Vertical,1,MOTOR 1,
J9,PinHeader_1x06_P2.54mm_Vertical,1,MOTOR 2,
L1,L_Wuerth_WE-TPC-3816,1,2.2u,
Q1,SOT-23-6,1,FS8205A,
Q2,SOT-23,1,DMP1045U-7,
R1,0603,1,1k2,
"R12, R13, R15",0603,3,330R,
"R14, R2",0603,2,1k,
"R16, R17, R7",0603,3,10k,
"R3, R4",0603,2,5.1k,
R5,0603,1,100R,
R6,0603,1,2k,
R8,0603,1,1M,
R9,0603,1,178k,
SW1,SW_SPDT_PCM12,1,SW_SPDT,
U1,Arduino_Nano,1,NUCLEO-G431KB,
U2,DIP-16_W10.16mm_LongPads,1,DRIVER 1,
U3,SOT-23-6,1,HY2112,
U4,SOIC-8-1EP_3.9x4.9mm_P1.27mm_EP2.29x3mm,1,CN3058E,
U5,Texas_DRC0010J_ThermalVias,1,TPS63000,
U6,DIP-16_W10.16mm_LongPads,1,DRIVER 2,

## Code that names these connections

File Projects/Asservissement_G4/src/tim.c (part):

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
    __HAL_RCC_GPIOA_CLK_ENABLE();
    /**TIM2 GPIO Configuration
    PA0     ------> TIM2_CH1
    PA1     ------> TIM2_CH2
    */
    GPIO_InitStruct.Pin = GPIO_PIN_0|GPIO_PIN_1;
    GPIO_InitStruct.Mode = GPIO_MODE_AF_PP;
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
    __HAL_RCC_GPIOA_CLK_ENABLE();
    /**TIM3 GPIO Configuration
    PA4     ------> TIM3_CH2
    PA6     ------> TIM3_CH1
    */
    GPIO_InitStruct.Pin = GPIO_PIN_4|GPIO_PIN_6;
    GPIO_InitStruct.Mode = GPIO_MODE_AF_PP;
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  /* USER CODE END TIM1_MspPostInit 0 */
    __HAL_RCC_GPIOA_CLK_ENABLE();
    /**TIM1 GPIO Configuration
    PA8     ------> TIM1_CH1
    PA11     ------> TIM1_CH1N
    */
    GPIO_InitStruct.Pin = GPIO_PIN_8|GPIO_PIN_11;
    GPIO_InitStruct.Mode = GPIO_MODE_AF_PP;
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    __HAL_RCC_GPIOA_CLK_ENABLE();
    __HAL_RCC_GPIOB_CLK_ENABLE();
    /**TIM16 GPIO Configuration
    PA12     ------> TIM16_CH1
    PB6     ------> TIM16_CH1N
    */
    GPIO_InitStruct.Pin = GPIO_PIN_12;
    GPIO_InitStruct.Mode = GPIO_MODE_AF_PP;
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    __HAL_RCC_TIM2_CLK_DISABLE();

    /**TIM2 GPIO Configuration
    PA0     ------> TIM2_CH1
    PA1     ------> TIM2_CH2
    */
    HAL_GPIO_DeInit(GPIOA, GPIO_PIN_0|GPIO_PIN_1);

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    __HAL_RCC_TIM3_CLK_DISABLE();

    /**TIM3 GPIO Configuration
    PA4     ------> TIM3_CH2
    PA6     ------> TIM3_CH1
    */
    HAL_GPIO_DeInit(GPIOA, GPIO_PIN_4|GPIO_PIN_6);

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
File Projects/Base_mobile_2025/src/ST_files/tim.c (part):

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
    __HAL_RCC_GPIOA_CLK_ENABLE();
    /**TIM1 GPIO Configuration
    PA8     ------> TIM1_CH1
    PA9     ------> TIM1_CH2
    */
    GPIO_InitStruct.Pin = ENC_1A_Pin|ENC_1B_Pin;
    GPIO_InitStruct.Mode = GPIO_MODE_AF_PP;
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
    __HAL_RCC_GPIOA_CLK_ENABLE();
    /**TIM2 GPIO Configuration
    PA0     ------> TIM2_CH1
    PA1     ------> TIM2_CH2
    */
    GPIO_InitStruct.Pin = ENC_2A_Pin|ENC_2B_Pin;
    GPIO_InitStruct.Mode = GPIO_MODE_AF_PP;
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
    __HAL_RCC_GPIOA_CLK_ENABLE();
    /**TIM3 GPIO Configuration
    PA4     ------> TIM3_CH2
    PA6     ------> TIM3_CH1
    */
    GPIO_InitStruct.Pin = ENC_3B_Pin|ENC_3A_Pin;
    GPIO_InitStruct.Mode = GPIO_MODE_AF_PP;
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  /* USER CODE END TIM4_MspPostInit 0 */
    __HAL_RCC_GPIOB_CLK_ENABLE();
    /**TIM4 GPIO Configuration
    PB7     ------> TIM4_CH2
    */
    GPIO_InitStruct.Pin = PWM_1_Pin;
    GPIO_InitStruct.Mode = GPIO_MODE_AF_PP;
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
    __HAL_RCC_GPIOB_CLK_ENABLE();
    /**TIM8 GPIO Configuration
    PB6     ------> TIM8_CH1
    */
    GPIO_InitStruct.Pin = PWM_2_Pin;
    GPIO_InitStruct.Mode = GPIO_MODE_AF_PP;
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    __HAL_RCC_TIM1_CLK_DISABLE();

    /**TIM1 GPIO Configuration
    PA8     ------> TIM1_CH1
    PA9     ------> TIM1_CH2
    */
    HAL_GPIO_DeInit(GPIOA, ENC_1A_Pin|ENC_1B_Pin);

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    __HAL_RCC_TIM2_CLK_DISABLE();

    /**TIM2 GPIO Configuration
    PA0     ------> TIM2_CH1
    PA1     ------> TIM2_CH2
    */
    HAL_GPIO_DeInit(GPIOA, ENC_2A_Pin|ENC_2B_Pin);

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    __HAL_RCC_TIM3_CLK_DISABLE();

    /**TIM3 GPIO Configuration
    PA4     ------> TIM3_CH2
    PA6     ------> TIM3_CH1
    */
    HAL_GPIO_DeInit(GPIOA, ENC_3B_Pin|ENC_3A_Pin);

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
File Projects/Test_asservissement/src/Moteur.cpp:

/* NUCLEO-G431KB - RÉGULATION PID MOTEUR SIMPLE
 * PID en boucle fermée avec un seul moteur + encodeur TIM2
 * Moteur: D9=PA8 (+), D3=PB0 (-)
 * Encodeur: A0=PA0 (TIM2_CH1), A1=PA1 (TIM2_CH2)
 */

#include <Arduino.h>
extern "C" {
  #include "stm32g4xx_hal.h"  // Changé de stm32l4xx_hal.h
}

// Pins PWM pour moteur (seulement le droit)
const uint8_t M_PWM_P = D9;   // TIM1_CH1  (PA8)  - Moteur +
const uint8_t M_PWM_N = D3;   // TIM1_CH2N (PB0)  - Moteur -

// Encodeur TIM2 (moteur droit)
TIM_HandleTypeDef htim2;
// Encodeur TIM3 (moteur gauche - D11/D12)
TIM_HandleTypeDef htim3;
static constexpr uint32_t ENC_MID = 0x7FFFFFFFUL;

// Paramètres encodeur
static constexpr float CPR_MOTOR = 1200.0f;  // Impulsions par tour moteur
static constexpr float GEAR_RATIO = 100.0f;  // Réducteur 100:1
static constexpr float QUAD_FACTOR = 4.0f;   // Mode encodeur X4
static constexpr float TICKS_PER_REV = (CPR_MOTOR * QUAD_FACTOR) / GEAR_RATIO; // = 48 ticks/tour roue

// Paramètres PID
static constexpr float DT_S = 0.050f; // 50ms période PID

// Gains PID (ajustés pour votre moteur)
float kp = 0.8f;  // Proportionnel
float ki = 0.2f;  // Intégral  
float kd = 0.1f;  // Dérivée

// Variables PID
float targetSpeed_rps = 0.0f;  // Consigne vitesse en tr/s
float currentSpeed_rps = 0.0f; // Vitesse mesurée
float error = 0.0f, errorPrev = 0.0f, errorSum = 0.0f;
float pidOutput = 0.0f;

// Variables encodeur moteur droit
int32_t encoderCount = 0, lastEncoderCount = 0;
// Variables encodeur moteur gauche
int32_t encoderCountLeft = 0, lastEncoderCountLeft = 0;
float currentSpeedLeft_rps = 0.0f;
unsigned long compteur = 0;

// Configuration encodeur TIM2
void MX_TIM2_Encoder_Init() {
  __HAL_RCC_GPIOA_CLK_ENABLE();
  __HAL_RCC_TIM2_CLK_ENABLE();

  GPIO_InitTypeDef GPIO_InitStruct{};
  GPIO_InitStruct.Pin       = GPIO_PIN_0 | GPIO_PIN_1;
  GPIO_InitStruct.Mode      = GPIO_MODE_AF_PP;
  GPIO_InitStruct.Pull      = GPIO_PULLUP;
  GPIO_InitStruct.Speed     = GPIO_SPEED_FREQ_HIGH;
  GPIO_InitStruct.Alternate = GPIO_AF1_TIM2;
  HAL_GPIO_Init(GPIOA, &GPIO_InitStruct);

  TIM_Encoder_InitTypeDef sConfig{};
  sConfig.EncoderMode = TIM_ENCODERMODE_TI12;
  sConfig.IC1Polarity  = TIM_INPUTCHANNELPOLARITY_RISING;
  sConfig.IC1Selection = TIM_ICSELECTION_DIRECTTI;
  sConfig.IC1Prescaler = TIM_ICPSC_DIV1;
  sConfig.IC1Filter    = 2;
  sConfig.IC2Polarity  = TIM_INPUTCHANNELPOLARITY_RISING;
  sConfig.IC2Selection = TIM_ICSELECTION_DIRECTTI;
  sConfig.IC2Prescaler = TIM_ICPSC_DIV1;
  sConfig.IC2Filter    = 2;

  htim2.Instance = TIM2;
  htim2.Init.Prescaler         = 0;
  htim2.Init.CounterMode       = TIM_COUNTERMODE_UP;
  htim2.Init.Period            = 0xFFFFFFFFUL;
  htim2.Init.ClockDivision     = TIM_CLOCKDIVISION_DIV1;
  htim2.Init.RepetitionCounter = 0;
  htim2.Init.AutoReloadPreload = TIM_AUTORELOAD_PRELOAD_DISABLE;

  HAL_TIM_Encoder_Init(&htim2, &sConfig);
  __HAL_TIM_SET_COUNTER(&htim2, ENC_MID);
  HAL_TIM_Encoder_Start(&htim2, TIM_CHANNEL_ALL);
}

// Configuration encodeur TIM3 (moteur gauche - D11/D12)
void MX_TIM3_Encoder_Init() {
  __HAL_RCC_GPIOB_CLK_ENABLE();
  __HAL_RCC_TIM3_CLK_ENABLE();

  // D11 = PB4 (TIM3_CH1), D12 = PB5 (TIM3_CH2)
  GPIO_InitTypeDef GPIO_InitStruct{};
  GPIO_InitStruct.Pin       = GPIO_PIN_4 | GPIO_PIN_5;
  GPIO_InitStruct.Mode      = GPIO_MODE_AF_PP;
  GPIO_InitStruct.Pull      = GPIO_PULLUP;
  GPIO_InitStruct.Speed     = GPIO_SPEED_FREQ_HIGH;
  GPIO_InitStruct.Alternate = GPIO_AF2_TIM3;
  HAL_GPIO_Init(GPIOB, &GPIO_InitStruct);

  TIM_Encoder_InitTypeDef sConfig{};
  sConfig.EncoderMode = TIM_ENCODERMODE_TI12;
  sConfig.IC1Polarity  = TIM_INPUTCHANNELPOLARITY_RISING;
  sConfig.IC1Selection = TIM_ICSELECTION_DIRECTTI;
  sConfig.IC1Prescaler = TIM_ICPSC_DIV1;
  sConfig.IC1Filter    = 2;
  sConfig.IC2Polarity  = TIM_INPUTCHANNELPOLARITY_RISING;
  sConfig.IC2Selection = TIM_ICSELECTION_DIRECTTI;
  sConfig.IC2Prescaler = TIM_ICPSC_DIV1;
  sConfig.IC2Filter    = 2;

  htim3.Instance = TIM3;
  htim3.Init.Prescaler         = 0;
  htim3.Init.CounterMode       = TIM_COUNTERMODE_UP;
  htim3.Init.Period            = 0xFFFFFFFFUL;
  htim3.Init.ClockDivision     = TIM_CLOCKDIVISION_DIV1;
  htim3.Init.RepetitionCounter = 0;
  htim3.Init.AutoReloadPreload = TIM_AUTORELOAD_PRELOAD_DISABLE;

  HAL_TIM_Encoder_Init(&htim3, &sConfig);
  __HAL_TIM_SET_COUNTER(&htim3, ENC_MID);
  HAL_TIM_Encoder_Start(&htim3, TIM_CHANNEL_ALL);
}

// Appliquer commande PWM moteur
void setMotorPWM(float cmd) {
  // Saturer à ±255
  if (cmd > 255.0f) cmd = 255.0f;
  if (cmd < -255.0f) cmd = -255.0f;
  
  if (cmd >= 0) {
    analogWrite(M_PWM_P, (int)cmd);
    analogWrite(M_PWM_N, 0);
  } else {
    analogWrite(M_PWM_P, 0);
    analogWrite(M_PWM_N, (int)(-cmd));
  }
}

void setup() {
  Serial.begin(115200);
  
  pinMode(M_PWM_P, OUTPUT);
  pinMode(M_PWM_N, OUTPUT);
  pinMode(LED_BUILTIN, OUTPUT);
  digitalWrite(LED_BUILTIN, HIGH);
  
  MX_TIM2_Encoder_Init();
  MX_TIM3_Encoder_Init();
  
  delay(1000);
  
  Serial.println("=== RÉGULATION PID MOTEUR ===");
  Serial.println("Moteur: D9(+) / D3(-)");
  Serial.println("Encodeur droit: A0/A1 (TIM2)");
  Serial.println("Encodeur gauche: D11/D12 (TIM3)");
  Serial.println("Consignes automatiques...");
  Serial.println("==============================");
  
  setMotorPWM(0); // Moteur arrêté
}

void loop() {
  static unsigned long lastPidTime = 0;
  static unsigned long lastDisplayTime = 0;
  static bool ledState = false;
  static uint8_t targetPhase = 0;
  
  // Lecture encodeur droit
  uint32_t rawCount = __HAL_TIM_GET_COUNTER(&htim2);
  encoderCount = (int32_t)rawCount - (int32_t)ENC_MID;
  
  // Lecture encodeur gauche
  uint32_t rawCountLeft = __HAL_TIM_GET_COUNTER(&htim3);
  encoderCountLeft = (int32_t)rawCountLeft - (int32_t)ENC_MID;
  
  // Calcul PID toutes les 50ms
  if (millis() - lastPidTime >= (unsigned long)(DT_S * 1000)) {
    
    // Calculer vitesse actuelle moteur droit en tr/s
    int32_t deltaEnc = encoderCount - lastEncoderCount;
    lastEncoderCount = encoderCount;
    currentSpeed_rps = (float)deltaEnc / TICKS_PER_REV / DT_S;
    
    // Calculer vitesse actuelle moteur gauche en tr/s
    int32_t deltaEncLeft = encoderCountLeft - lastEncoderCountLeft;
    lastEncoderCountLeft = encoderCountLeft;
    currentSpeedLeft_rps = (float)deltaEncLeft / TICKS_PER_REV / DT_S;
    
    // Calcul PID
    error = targetSpeed_rps - currentSpeed_rps;
    errorSum += error * DT_S;
    float errorDiff = (error - errorPrev) / DT_S;
    
    pidOutput = kp * error + ki * errorSum + kd * errorDiff;
    errorPrev = error;
    
    // Saturation anti-windup simple
    if (errorSum > 100.0f) errorSum = 100.0f;
    if (errorSum < -100.0f) errorSum = -100.0f;
    
    // Appliquer au moteur
    setMotorPWM(pidOutput);
    
    lastPidTime = millis();
  }
  
  // Affichage + changement consigne toutes les 200ms
  if (millis() - lastDisplayTime >= 200) {
    compteur++;
    ledState = !ledState;
    digitalWrite(LED_BUILTIN, ledState ? LOW : HIGH);
    
    // Changer consigne toutes les 25 fois (5 secondes)
    if (compteur % 25 == 0) {
      targetPhase = (targetPhase + 1) % 5;
      
      switch(targetPhase) {
        case 0: targetSpeed_rps = 0.0f; Serial.println(">> CONSIGNE: 0 tr/s (ARRÊT)"); break;
        case 1: targetSpeed_rps = 30.0f; Serial.println(">> CONSIGNE: 1 tr/s (LENT +)"); break;
        case 2: targetSpeed_rps = 0.0f; Serial.println(">> CONSIGNE: -1 tr/s (LENT -)"); break;
        case 3: targetSpeed_rps = -30.0f; Serial.println(">> CONSIGNE: 2 tr/s (RAPIDE +)"); break;
        case 4: targetSpeed_rps = -50.0f; Serial.println(">> CONSIGNE: -2 tr/s (RAPIDE -)"); break;
      }
      // Reset intégrateur à chaque changement
      errorSum = 0.0f;
    }
    
    // Affichage PID
    Serial.print("Consigne: ");
    Serial.print(targetSpeed_rps, 1);
    Serial.print(" | Mesure D: ");
    Serial.print(currentSpeed_rps, 2);
    Serial.print(" | Mesure G: ");
    Serial.print(currentSpeedLeft_rps, 2);
    Serial.print(" | Erreur: ");
    Serial.print(error, 2);
    Serial.print(" | PWM: ");
    Serial.print(pidOutput, 0);
    Serial.print(" | Enc D: ");
    Serial.print(encoderCount);
    Serial.print(" | Enc G: ");
    Serial.println(encoderCountLeft);
    
    lastDisplayTime = millis();
  }
  
  delay(10);
}

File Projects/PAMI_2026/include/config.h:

#ifndef CONFIG_H
#define CONFIG_H

#include <Arduino.h>

// --- PINS DEFINITIONS ---
// UART STM32
#define PIN_RX2       16
#define PIN_TX2       17

// I2C SENSORS
#define PIN_SDA       21
#define PIN_SCL       22
// TOF XSHUT (LPN)
#define PIN_TOF1_LPN  4
#define PIN_TOF2_LPN  23
#define PIN_TOF3_LPN  18

// Actionneurs
#define PIN_SERVO_1   19
#define PIN_SERVO_2   15
#define PIN_SERVO_3   27
#define PIN_LED_DATA  14
#define PIN_MOT1_DIR1  32 // Moteur direct 1
#define PIN_MOT1_DIR2  33
#define PIN_MOT2_DIR1  25 // Moteur direct 2
#define PIN_MOT2_DIR2  26

// INPUTS
#define PIN_TIRETTE   39 // À définir (Pull-up interne requis)
#define PIN_SW_COLOR  34 // Input Only
#define PIN_SW_DEBUG  35 // Input Only
#define PIN_SW_MODE   36 // "UP" - Souvent VP/VN (Input Only)

// --- CONSTANTS ---
#define MATCH_DURATION_MS 99000 // 99 secondes (marge sécu)
#define BATTERY_MIN_V     3.0f  // Seuil alerte (par cellule, ou total à adapter)
#define BATTERY_TIMEOUT   1000  // Temps min sous le seuil pour déclencher l'erreur

// --- TOF GEOMETRY (Matriciels 8x8) ---
// Ordre des capteurs dans le code : [0]=TOF2(Gauche), [1]=TOF3(Centre), [2]=TOF1(Droite)
// On lit uniquement la ligne du milieu pour économiser la puissance GPU
// Angles en degrés, orientation : 0°=devant, +90°=gauche, -90°=droite (convention robot)

#define TOF_ANGLE_GAUCHE  -55.5f  // TOF2 : tourné 55.5° à gauche
#define TOF_FOV_GAUCHE    60.0f   // 60° de champ

#define TOF_ANGLE_CENTRE  0.0f    // TOF3 : au centre
#define TOF_FOV_CENTRE    45.0f   // 45° de champ

#define TOF_ANGLE_DROITE  55.5f   // TOF1 : tourné 55.5° à droite
#define TOF_FOV_DROITE    60.0f   // 60° de champ

// Paramètres de la matricielle : on lit seulement la ligne du milieu (8 zones par capteur)
#define TOF_ZONES_PER_LINE 8
#define TOF_LINE_MIDDLE    4      // Indice de la ligne du milieu dans la matrice 8x8

#endif

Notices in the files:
Projects/Asservissement_G4/src/tim.c:
Copyright (c) 2025 STMicroelectronics.
All rights reserved.
This software is licensed under terms that can be found in the LICENSE file
